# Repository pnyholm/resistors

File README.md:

resistors
=========

This repo contains the code used for the BYU ME 495R, Intro to Mechatronics, class robot competition. For a further description of the project, refer to theresistors.groups.et.byu.net

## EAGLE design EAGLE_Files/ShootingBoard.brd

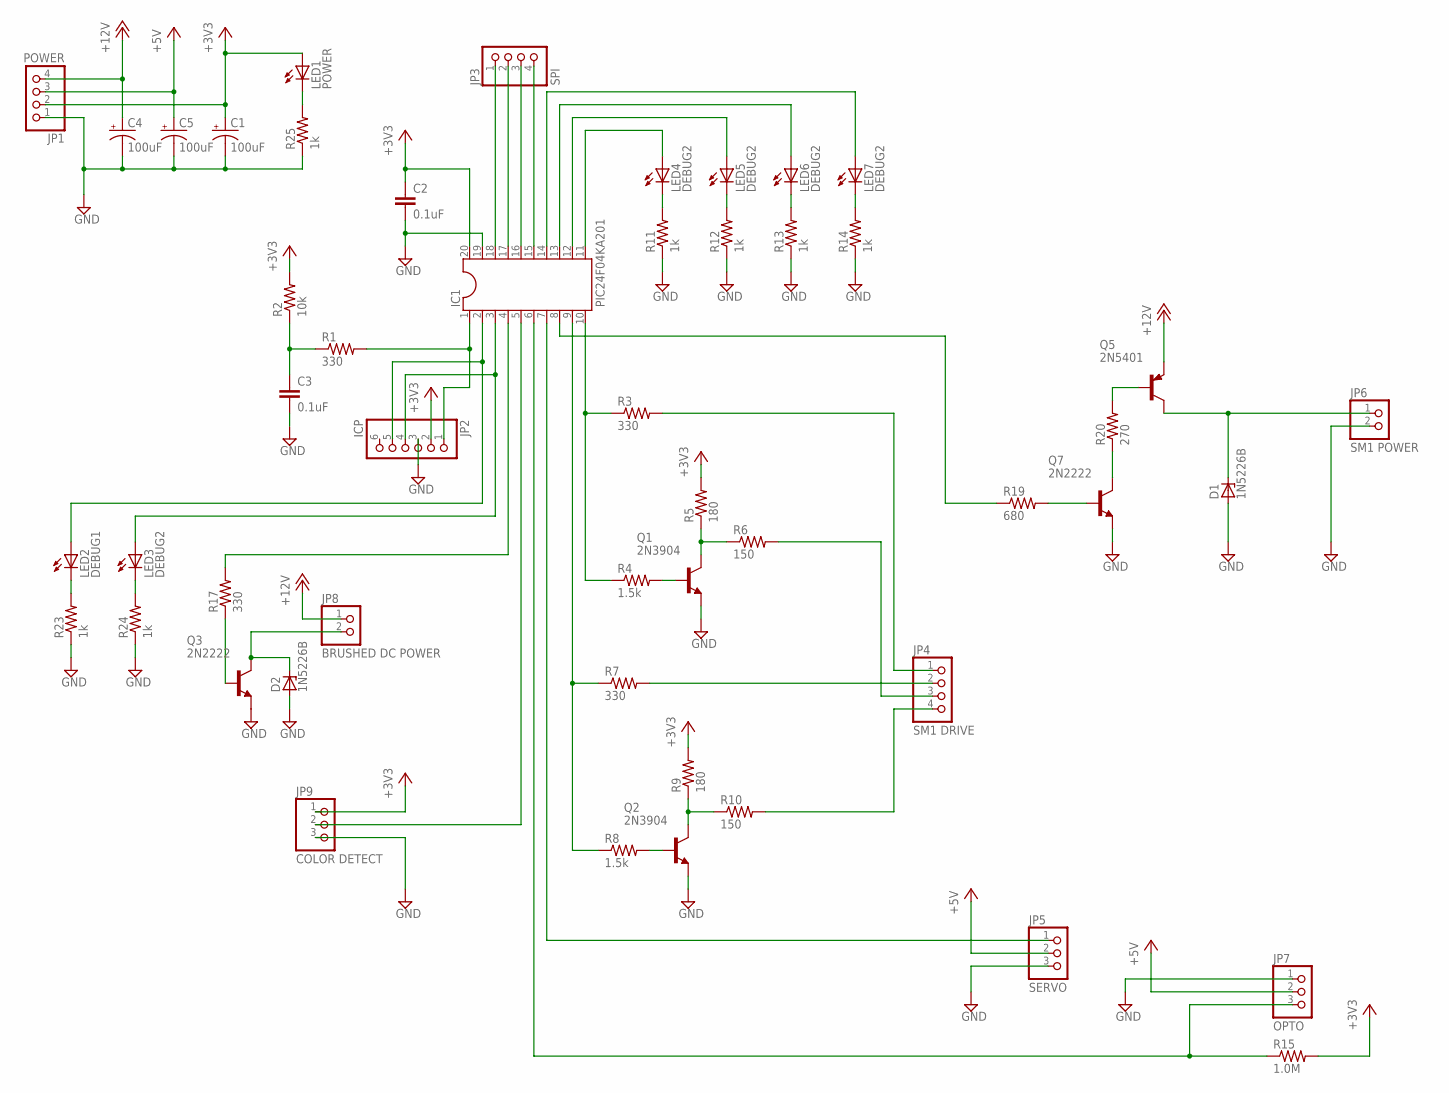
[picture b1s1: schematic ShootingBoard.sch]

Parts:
C1, C4, C5: 100uF; E2,5-7
C2, C3: 0.1uF; C0805
D1, D2: 1N5226B; DO35Z10
IC1: PIC24F04KA201; SOCKET-20
JP1: POWER; 1X04
JP2: ICP; 1X06
JP3: SPI; 1X04
JP4: SM1 DRIVE; 1X04
JP5: SERVO; 1X03
JP6: SM1 POWER; 1X02
JP7: OPTO; 1X03
JP8: BRUSHED DC POWER; 1X02
JP9: COLOR DETECT; 1X03
LED1: POWER; LED3MM
LED2: DEBUG1; LED3MM
LED3, LED4, LED5, LED6, LED7: DEBUG2; LED3MM
Q1, Q2: 2N3904; TO92
Q3, Q7: 2N2222; TO92
Q5: 2N5401; TO92
R1, R3, R7, R17: 330; R0805
R2: 10k; R0805
R4, R8: 1.5k; R0805
R5, R9: 180; R0805
R6, R10: 150; R0805
R11, R12, R13, R14, R23, R24, R25: 1k; R0805
R15: 1.0M; R0805
R19: 680; R0805
R20: 270; R0805

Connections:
+3V3: C1.+, C2.1, IC1.20, JP1.2, JP2.2, JP9.1, LED1.A, R2.2, R5.2, R9.2, R15.2
+5V: C5.+, JP1.3, JP5.2, JP7.2
+12V: C4.+, JP1.4, JP8.1, Q5.3 (E)
GND: C1.-, C2.2, C3.2, C4.-, C5.-, D1.A, D2.A, IC1.19, JP1.1, JP2.3, JP5.3, JP6.2, JP7.1, JP9.3, Q1.3 (E), Q2.3 (E), Q3.3 (E), Q7.3 (E), R11.1, R12.1, R13.1, R14.1, R23.1, R24.1, R25.1
unnamed: IC1.1, JP2.1, R1.2
unnamed: C3.1, R1.1, R2.1
unnamed: IC1.2, JP2.5, LED2.A
unnamed: IC1.3, JP2.4, LED3.A
unnamed: IC1.10, R3.1, R4.1
unnamed: Q1.1 (C), R5.1, R6.1
unnamed: Q1.2 (B), R4.2
unnamed: IC1.9, R7.1, R8.1
unnamed: Q2.1 (C), R9.1, R10.1
unnamed: Q2.2 (B), R8.2
unnamed: IC1.11, LED4.A
unnamed: LED4.K (C), R11.2
unnamed: IC1.12, LED5.A
unnamed: LED5.K (C), R12.2
unnamed: IC1.13, LED6.A
unnamed: LED6.K (C), R13.2
unnamed: JP4.1, R3.2
unnamed: JP4.2, R7.2
unnamed: JP4.3, R6.2
unnamed: JP4.4, R10.2
unnamed: IC1.14, LED7.A
unnamed: LED7.K (C), R14.2
unnamed: IC1.6, JP7.3, R15.1
unnamed: IC1.5, JP9.2
unnamed: IC1.4, R17.2
unnamed: Q7.1 (C), R20.1
unnamed: Q5.2 (B), R20.2
unnamed: D1.C, JP6.1, Q5.1 (C)
unnamed: D2.C, JP8.2, Q3.1 (C)
unnamed: IC1.7, JP5.1
unnamed: Q7.2 (B), R19.2
unnamed: Q3.2 (B), R17.1
unnamed: IC1.8, R19.1
unnamed: IC1.18, JP3.1
unnamed: IC1.17, JP3.2
unnamed: IC1.16, JP3.3
unnamed: IC1.15, JP3.4
unnamed: LED2.K (C), R23.2
unnamed: LED3.K (C), R24.2
unnamed: LED1.K (C), R25.2

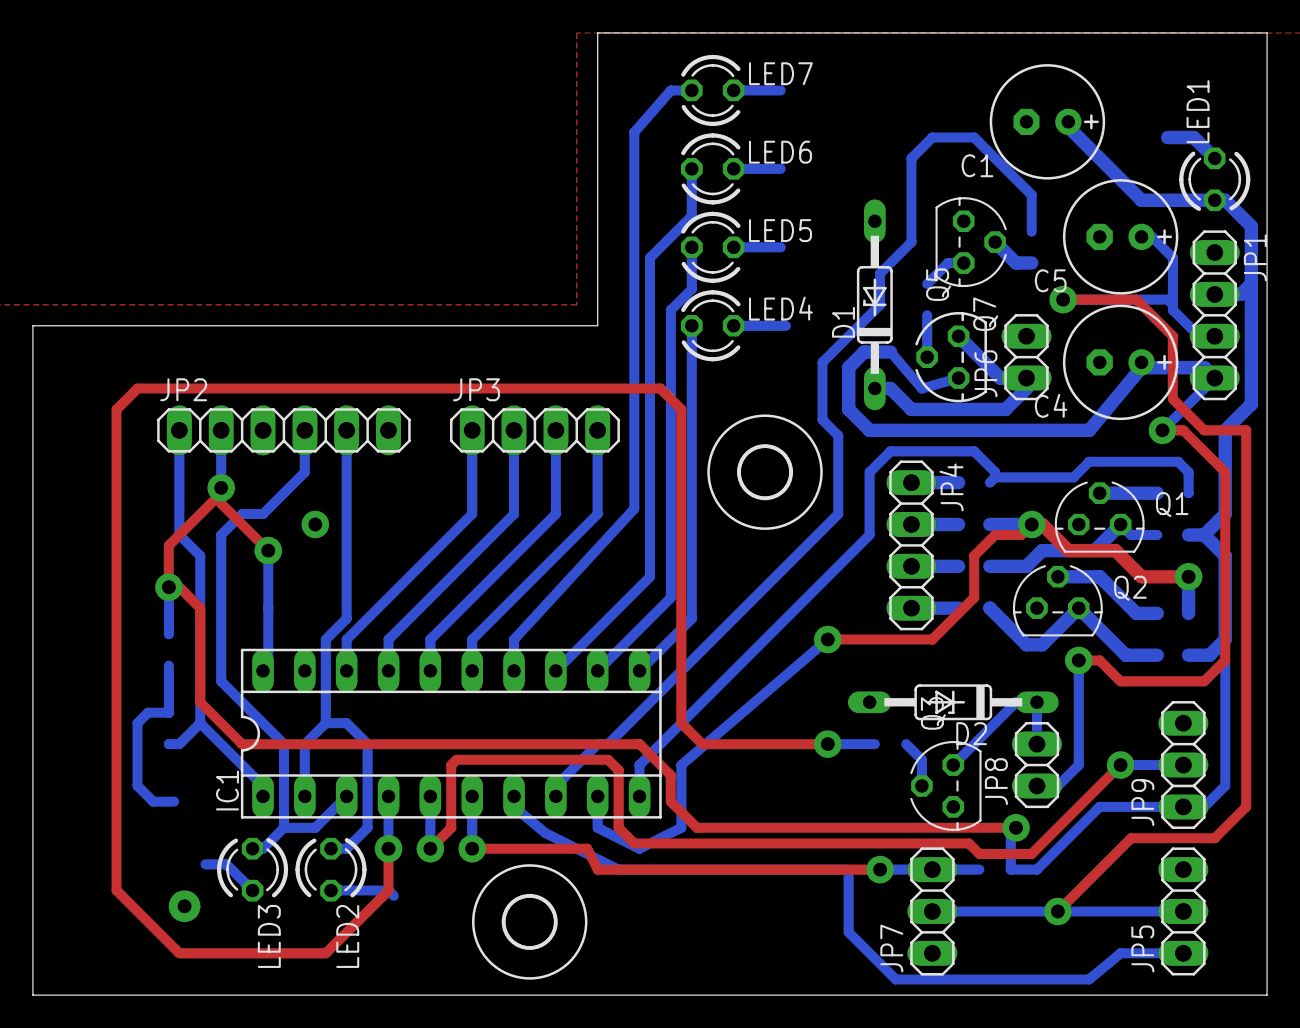
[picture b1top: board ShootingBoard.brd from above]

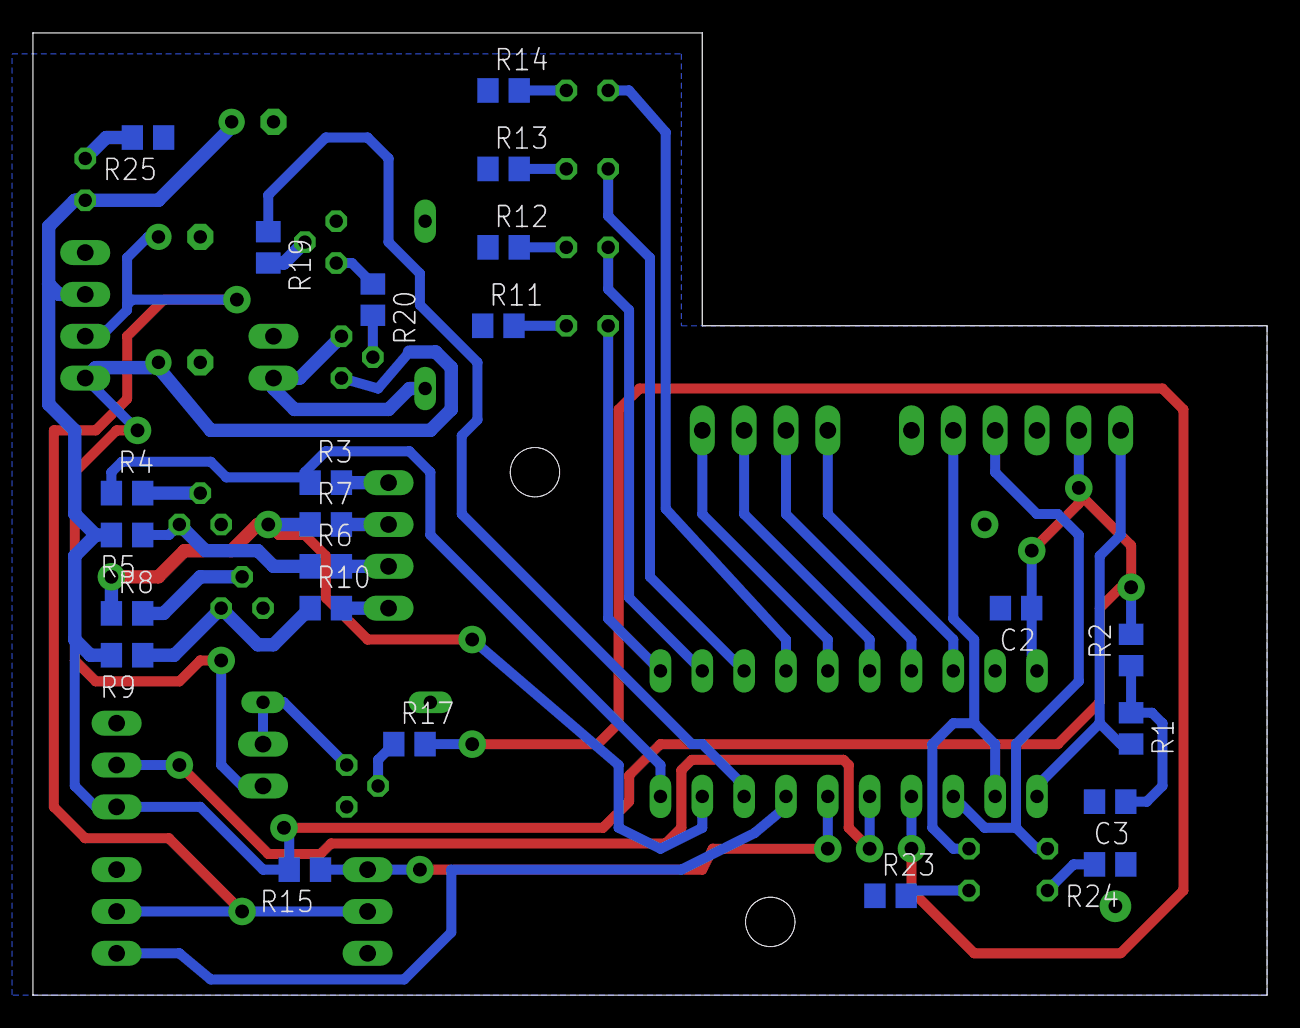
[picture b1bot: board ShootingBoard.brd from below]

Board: 2 copper layers, 74.9 x 58.4 mm, 52 parts (23 on the bottom side), 44 nets.

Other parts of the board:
U$1, U$2: 3,0

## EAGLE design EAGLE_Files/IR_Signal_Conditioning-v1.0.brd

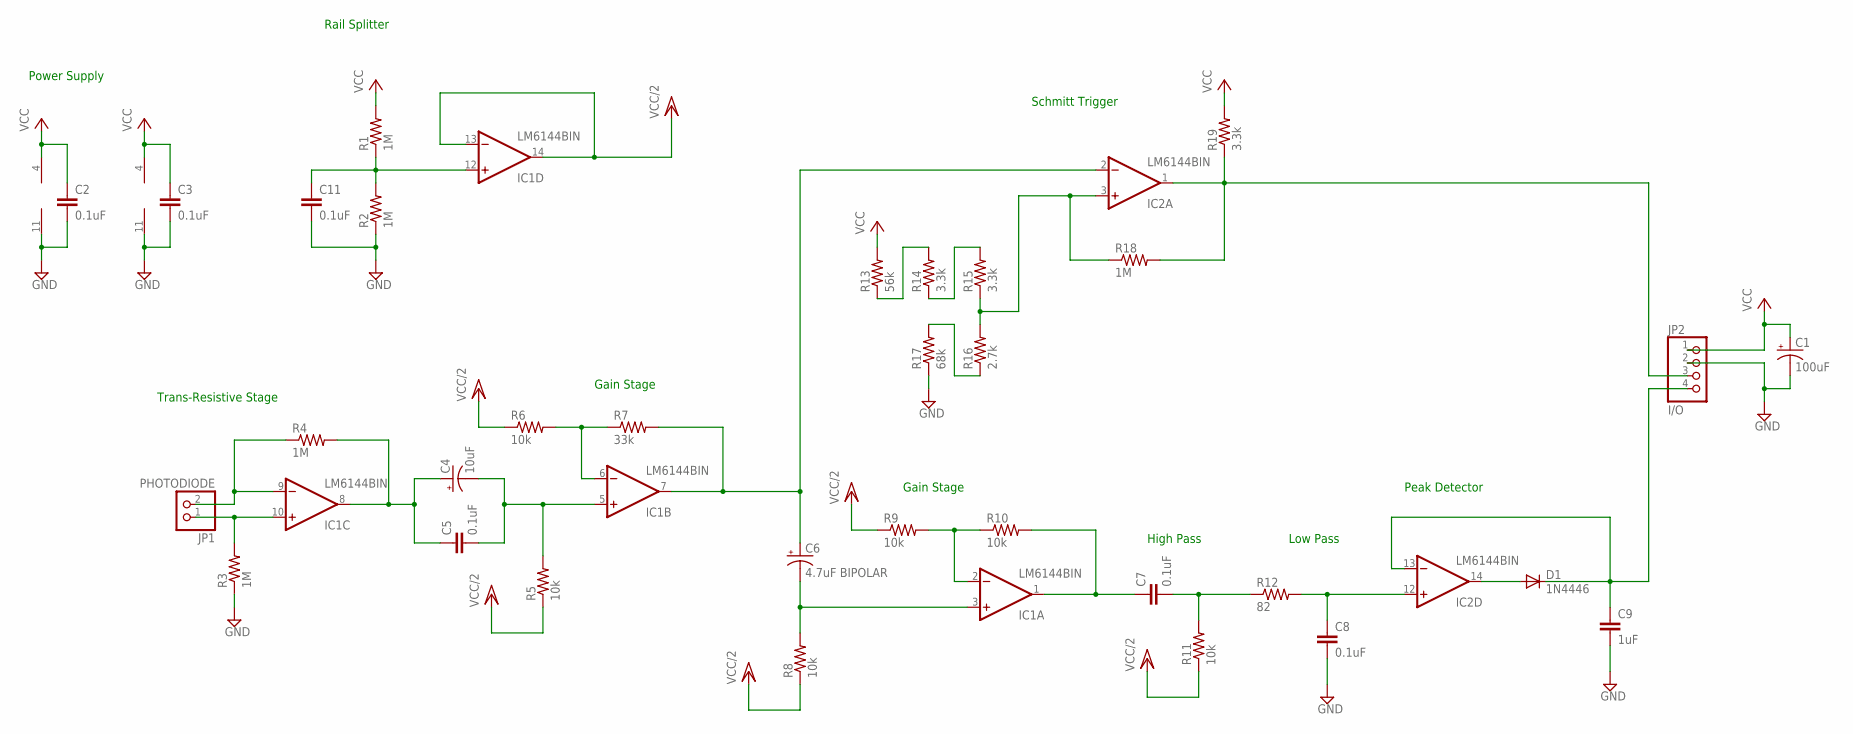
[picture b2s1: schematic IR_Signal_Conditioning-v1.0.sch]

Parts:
C1: 100uF; E2-5
C2, C3, C5, C7, C8, C11: 0.1uF; C0805
C4: 10uF; E2-5
C6: 4.7uF BIPOLAR; E2-5
C9: 1uF; C0805
D1: 1N4446; DO35-10
IC1, IC2: LM6144BIN; DIL14
JP1: PHOTODIODE; 1X02
JP2: I/O; 1X04
R1, R2, R3, R4, R18: 1M; R0805
R5, R6, R8, R9, R10, R11: 10k; R0805
R7: 33k; R0805
R12: 82; R0805
R13: 56k; R0805
R14, R15, R19: 3.3k; R0805
R16: 2.7k; R0805
R17: 68k; R0805

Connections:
GND: C1.-, C2.2, C3.2, C8.2, C9.2, C11.2, IC1.11 (V-), IC2.11 (V-), JP2.2, R2.1, R3.1, R17.1
unnamed: IC1.10 (+IN), JP1.1, R3.2
unnamed: IC1.9 (-IN), JP1.2, R4.1
unnamed: C4.+, C5.1, IC1.8 (OUT), R4.2
unnamed: C4.-, C5.2, IC1.5 (+IN), R5.2
unnamed: IC1.6 (-IN), R6.2, R7.1
unnamed: C6.+, IC1.7 (OUT), IC2.2 (-IN), R7.2
unnamed: C6.-, IC1.3 (+IN), R8.2
unnamed: IC1.2 (-IN), R9.2, R10.1
unnamed: C7.1, IC1.1 (OUT), R10.2
unnamed: C7.2, R11.2, R12.1
unnamed: D1.A, IC2.14 (OUT)
unnamed: C8.1, IC2.12 (+IN), R12.2
unnamed: C9.1, D1.C, IC2.13 (-IN), JP2.4
unnamed: R13.1, R14.2
unnamed: R14.1, R15.2
unnamed: IC2.3 (+IN), R15.1, R16.2, R18.1
unnamed: R16.1, R17.2
unnamed: IC2.1 (OUT), JP2.3, R18.2, R19.1
unnamed: C11.1, IC1.12 (+IN), R1.1, R2.2
VCC: C1.+, C2.1, C3.1, IC1.4 (V+), IC2.4 (V+), JP2.1, R1.2, R13.2, R19.2
VCC/2: IC1.13 (-IN), IC1.14 (OUT), R5.1, R6.1, R8.1, R9.1, R11.1

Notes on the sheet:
Schmitt Trigger
Trans-Resistive Stage
Gain Stage
Peak Detector
Rail Splitter
High Pass
Low Pass
Power Supply

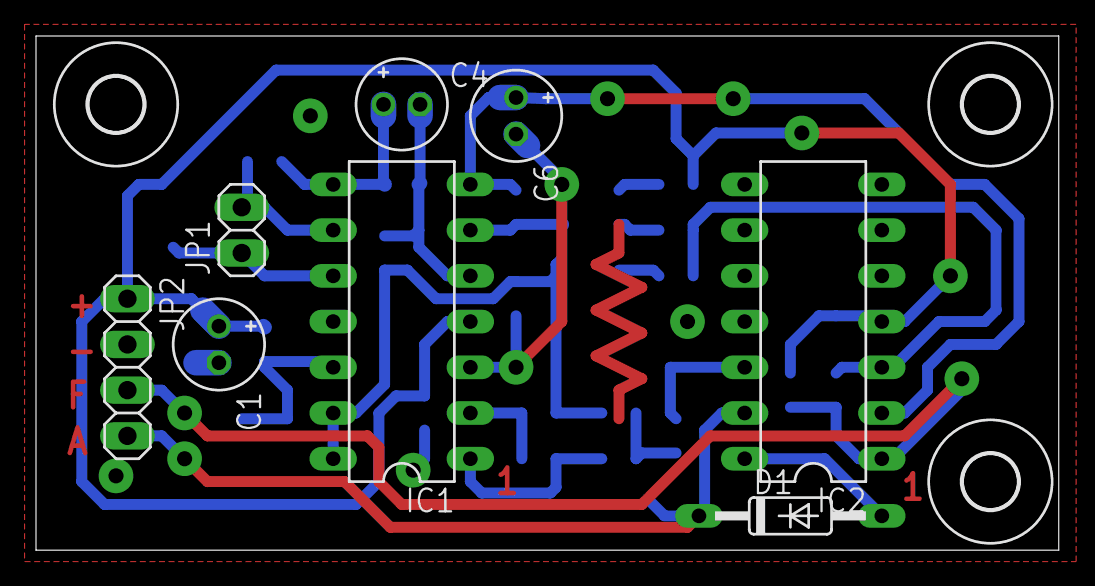
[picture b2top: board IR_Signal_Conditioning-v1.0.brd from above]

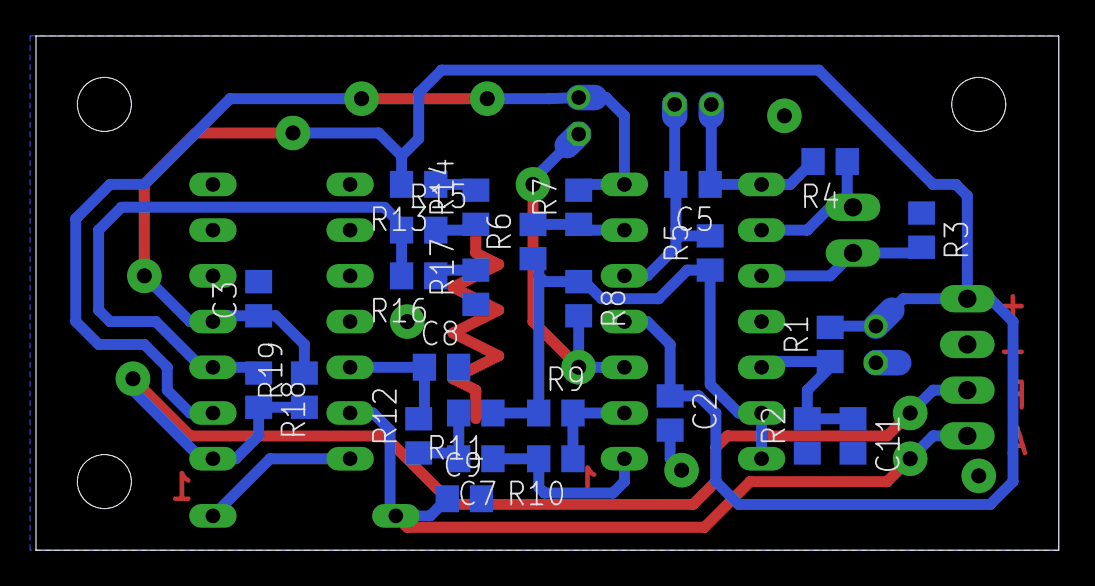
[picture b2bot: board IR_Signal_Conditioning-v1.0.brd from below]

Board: 2 copper layers, 56.8 x 28.6 mm, 37 parts (26 on the bottom side), 22 nets.

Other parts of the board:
U$1, U$2, U$3: 3,0

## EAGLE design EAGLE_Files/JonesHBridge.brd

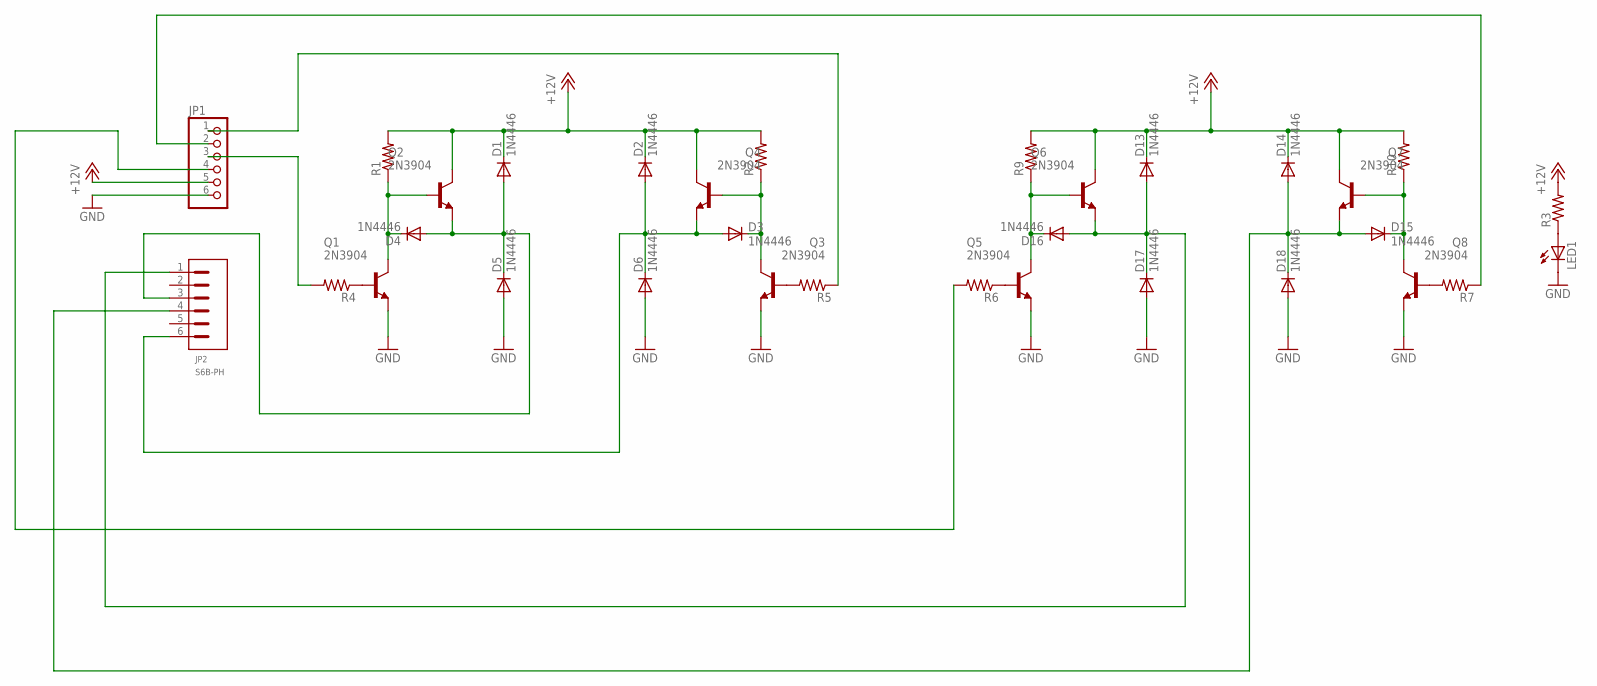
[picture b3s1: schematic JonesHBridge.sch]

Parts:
D1, D2, D3, D4, D5, D6, D13, D14, D15, D16, D17, D18: 1N4446; DO35-10
JP1: PINHD-1X6; 1X06
JP2: S6B-PH; S6B
LED1: LED3MM
Q1, Q2, Q3, Q4, Q5, Q6, Q7, Q8: 2N3904; TO92
R1, R2, R3, R4, R5, R6, R7, R9, R10: R-US_R0805; R0805

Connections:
+12V: D1.C, D2.C, D13.C, D14.C, JP1.5, Q2.1 (C), Q4.1 (C), Q6.1 (C), Q7.1 (C), R1.2, R2.2, R3.2, R9.2, R10.2
GND: D5.A, D6.A, D17.A, D18.A, JP1.6, LED1.K (C), Q1.3 (E), Q3.3 (E), Q5.3 (E), Q8.3 (E)
unnamed: D4.C, Q1.1 (C), Q2.2 (B), R1.1
unnamed: D1.A, D4.A, D5.C, JP2.3, Q2.3 (E)
unnamed: Q1.2 (B), R4.1
unnamed: LED1.A, R3.1
unnamed: Q5.2 (B), R6.1
unnamed: Q3.2 (B), R5.2
unnamed: D2.A, D3.A, D6.C, JP2.6, Q4.3 (E)
unnamed: D3.C, Q3.1 (C), Q4.2 (B), R2.1
unnamed: Q8.2 (B), R7.2
unnamed: D16.C, Q5.1 (C), Q6.2 (B), R9.1
unnamed: D15.C, Q7.2 (B), Q8.1 (C), R10.1
unnamed: D14.A, D15.A, D18.C, JP2.4, Q7.3 (E)
unnamed: D13.A, D16.A, D17.C, JP2.1, Q6.3 (E)
unnamed: JP1.3, R4.2
unnamed: JP1.1, R5.1
unnamed: JP1.2, R7.1
unnamed: JP1.4, R6.2

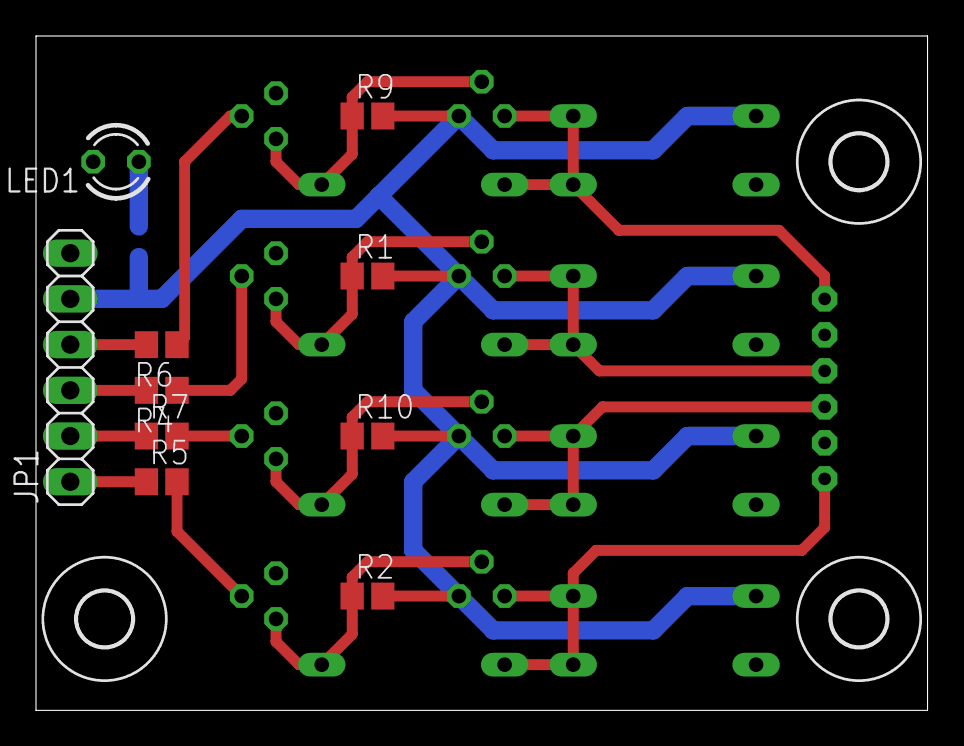
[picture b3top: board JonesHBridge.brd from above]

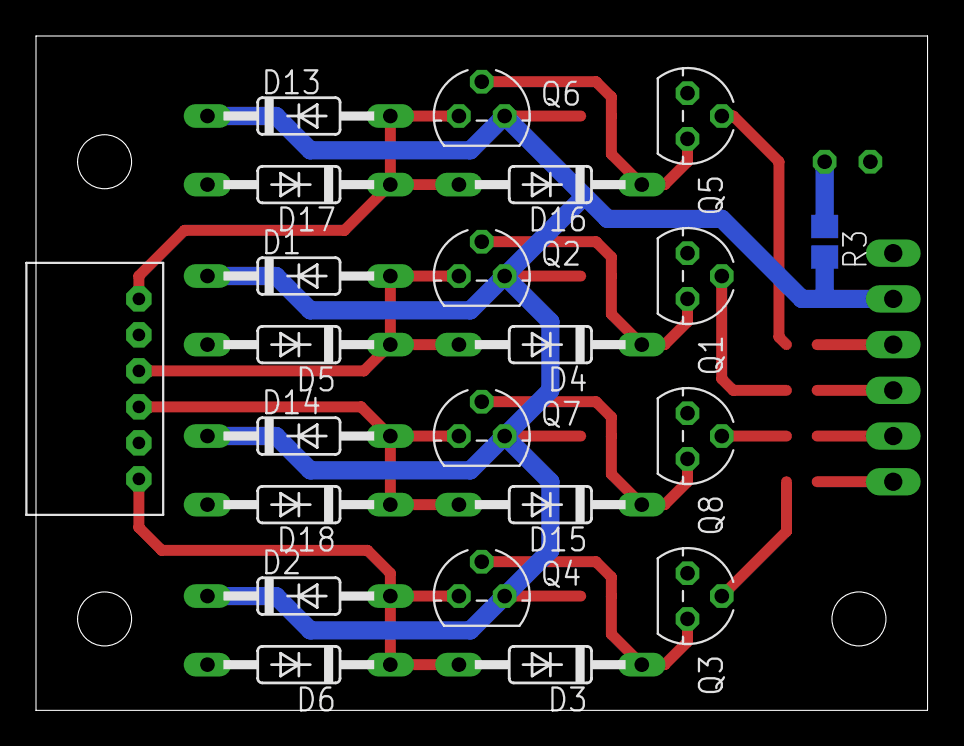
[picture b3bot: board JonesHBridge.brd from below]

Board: 2 copper layers, 49.5 x 37.5 mm, 35 parts (22 on the bottom side), 19 nets.

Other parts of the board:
U$1, U$2, U$3: 3,0

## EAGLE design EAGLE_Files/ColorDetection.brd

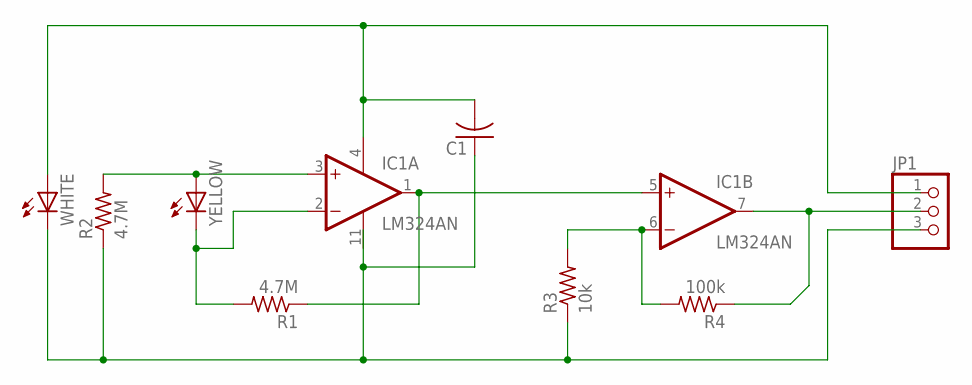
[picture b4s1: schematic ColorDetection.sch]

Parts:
C1: C-USC0805; C0805
IC1: LM324AN; DIL14
JP1: PINHD-1X3; 1X03
R1, R2: 4.7M; M0805
R3: 10k; M0805
R4: 100k; M0805
WHITE: LED10MM
YELLOW: LED5MM

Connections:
3V3: C1.2, IC1.4 (V+), JP1.1, WHITE.A
GND: C1.1, JP1.3, R2.1, R3.1, WHITE.K (C)
unnamed: IC1.3 (+IN), R2.2, YELLOW.A
unnamed: IC1.2 (-IN), R1.2, YELLOW.K (C)
unnamed: IC1.1 (OUT), IC1.5 (+IN), R1.1
unnamed: IC1.6 (-IN), R3.2, R4.2
unnamed: IC1.7 (OUT), JP1.2, R4.1
V-: IC1.11 (V-)

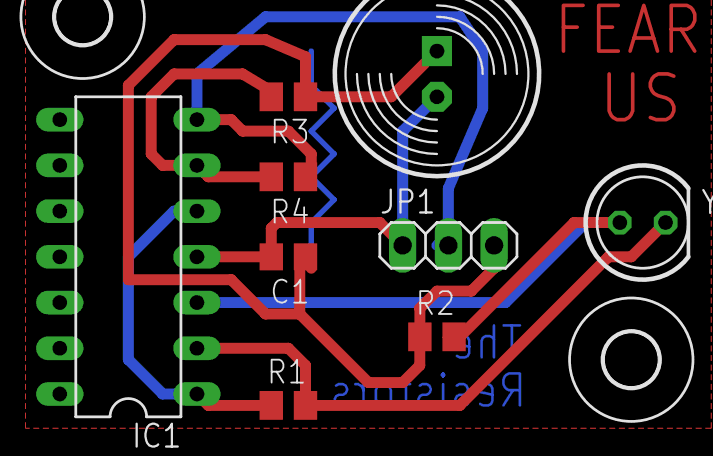
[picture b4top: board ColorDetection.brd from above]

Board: 2 copper layers, 11 parts (0 on the bottom side), 7 nets.

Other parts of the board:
U$1, U$2: 3,0

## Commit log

2013-07-19 Header for SPIconfiguration
2013-07-19 Source to configure SPI
2013-07-19 oops
2013-07-19 Header for SPI configuration
2013-07-22 Added directories for each of the modules (Navigation, Sorting, Shooting) as well as a directory for serial communication files since they will be included into all the modules
2013-07-22 Removed the leftover ConfigureSPI.c and ConfigureSPI.h
2013-07-27 updated SerialCom files to their latest state (slave still does not recieve the message correctly_), also added the RangeFinder code for the test board
2013-07-29 Send one byte of data, slave recieves correctly. Needs refining, but it works
2013-08-06 Create SERVO
2013-08-06 color detection. In progress.
2013-08-06 Color.c in progress
2013-08-09 It works now, needs to be tuned once it is mounted on the bot
2013-08-14 new file structure for repo and website
2013-08-14 got rid of old structure
